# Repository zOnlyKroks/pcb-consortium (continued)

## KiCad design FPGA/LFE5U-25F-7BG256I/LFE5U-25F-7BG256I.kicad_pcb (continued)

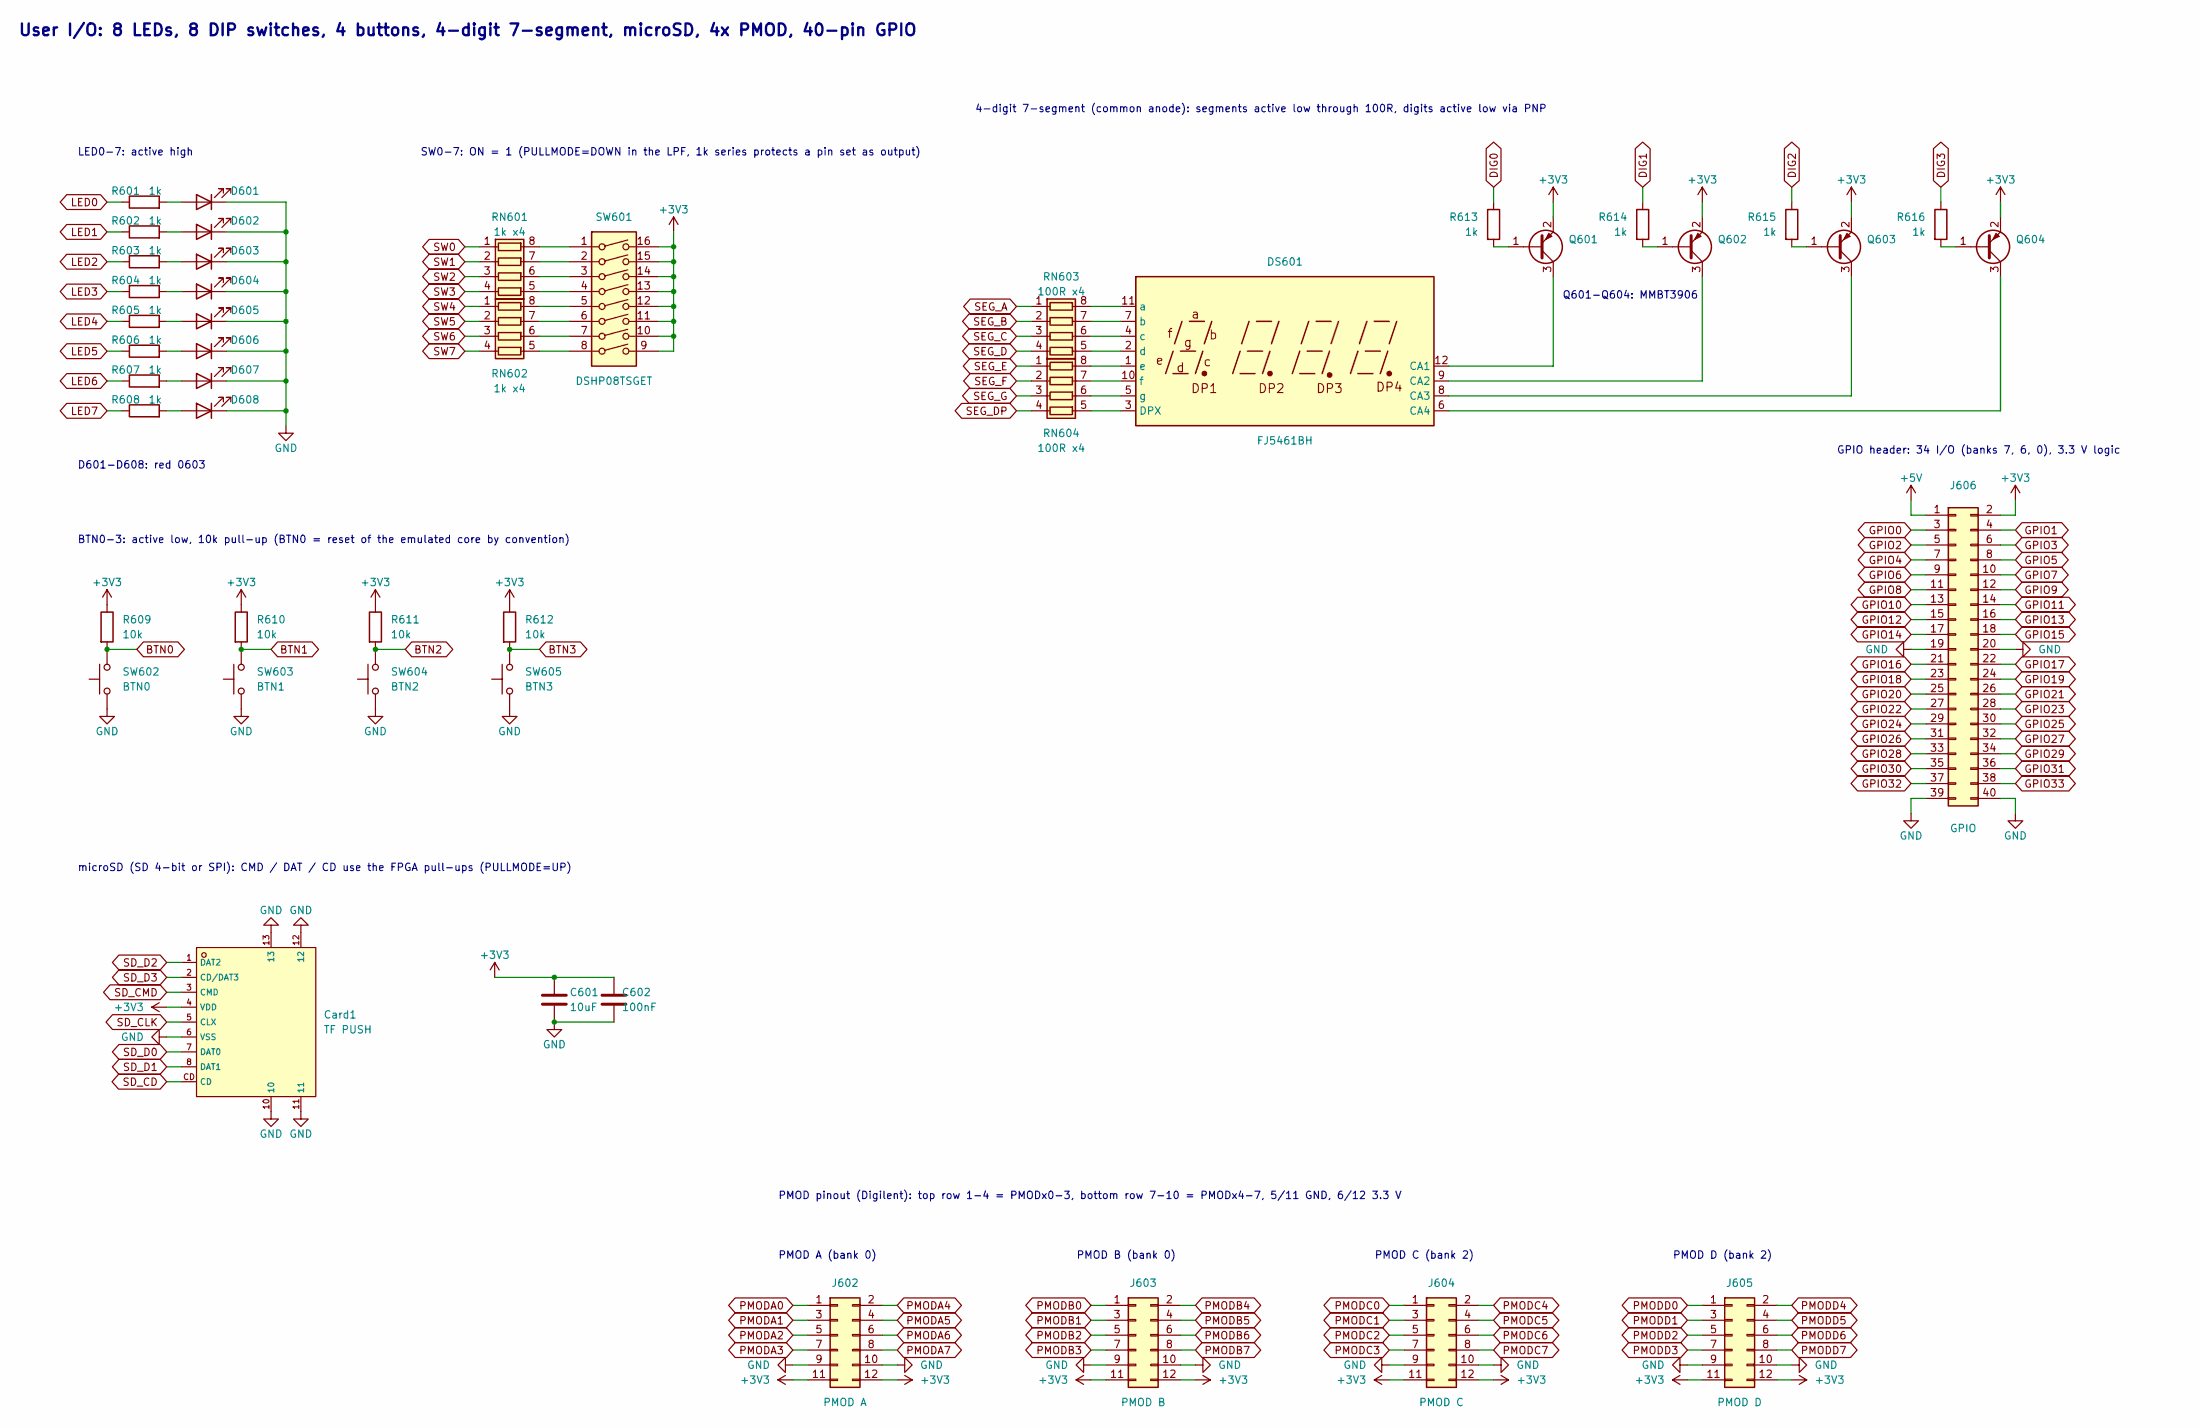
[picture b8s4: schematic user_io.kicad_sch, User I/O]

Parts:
C601: 10uF; C_0603_1608Metric; LCSC Part # C19702
C602: 100nF; C_0603_1608Metric; LCSC Part # C14663
Card1: TF PUSH; C393941_TF-SMD_TF-PUSH; LCSC C393941
D601, D602, D603, D604, D605, D606, D607, D608: LED red; LED_0603_1608Metric; LCSC Part # C2286
DS601: FJ5461BH; CA56-12EWA; LCSC Part # C38183
J602: PMOD A; PinSocket_2x06_P2.54mm_Horizontal; LCSC Part # C2897426
J603: PMOD B; PinSocket_2x06_P2.54mm_Horizontal; LCSC Part # C2897426
J604: PMOD C; PinSocket_2x06_P2.54mm_Horizontal; LCSC Part # C2897426
J605: PMOD D; PinSocket_2x06_P2.54mm_Horizontal; LCSC Part # C2897426
J606: GPIO; PinHeader_2x20_P2.54mm_Vertical; LCSC Part # C22465944
Q601, Q602, Q603, Q604: MMBT3906; SOT-23; LCSC Part # C53444
R601, R602, R603, R604, R605, R606, R607, R608, R613, R614, R615, R616: 1k; R_0603_1608Metric; LCSC Part # C22548
R609, R610, R611, R612: 10k; R_0603_1608Metric; LCSC Part # C25804
RN601, RN602: 1k x4; R_Array_Convex_4x0603; LCSC Part # C20197
RN603, RN604: 100R x4; R_Array_Convex_4x0603; LCSC Part # C25506
SW601: DSHP08TSGET; SW_DIP_SPSTx08_Slide_KingTek_DSHP08TS_W7.62mm_P1.27mm; LCSC Part # C40738
SW602: BTN0; SW_SPST_TL3342; LCSC Part # C318884
SW603: BTN1; SW_SPST_TL3342; LCSC Part # C318884
SW604: BTN2; SW_SPST_TL3342; LCSC Part # C318884
SW605: BTN3; SW_SPST_TL3342; LCSC Part # C318884

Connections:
+3V3: C601.1, C602.1, Card1.4 (VDD), J602.11, J602.12, J603.11, J603.12, J604.11, J604.12, J605.11, J605.12, J606.2, Q601.2 (E), Q602.2 (E), Q603.2 (E), Q604.2 (E), R609.1, R610.1, R611.1, R612.1, SW601.9, SW601.10, SW601.11, SW601.12, SW601.13, SW601.14, SW601.15, SW601.16; also elsewhere on the board
+5V: J606.1; also elsewhere on the board
BTN0: R609.2, SW602.2; also elsewhere on the board
BTN1: R610.2, SW603.2; also elsewhere on the board
BTN2: R611.2, SW604.2; also elsewhere on the board
BTN3: R612.2, SW605.2; also elsewhere on the board
DIG0: R613.1; also elsewhere on the board
DIG1: R614.1; also elsewhere on the board
DIG2: R615.1; also elsewhere on the board
DIG3: R616.1; also elsewhere on the board
GND: C601.2, C602.2, Card1.6 (VSS), Card1.10, Card1.11, Card1.12, Card1.13, D601.1 (K), D602.1 (K), D603.1 (K), D604.1 (K), D605.1 (K), D606.1 (K), D607.1 (K), D608.1 (K), J602.9, J602.10, J603.9, J603.10, J604.9, J604.10, J605.9, J605.10, J606.19, J606.20, J606.39, J606.40, SW602.1, SW603.1, SW604.1, SW605.1; also elsewhere on the board
GPIO0: J606.3; also elsewhere on the board
GPIO1: J606.4; also elsewhere on the board
GPIO2: J606.5; also elsewhere on the board
GPIO3: J606.6; also elsewhere on the board
GPIO4: J606.7; also elsewhere on the board
GPIO5: J606.8; also elsewhere on the board
GPIO6: J606.9; also elsewhere on the board
GPIO7: J606.10; also elsewhere on the board
GPIO8: J606.11; also elsewhere on the board
GPIO9: J606.12; also elsewhere on the board
GPIO10: J606.13; also elsewhere on the board
GPIO11: J606.14; also elsewhere on the board
GPIO12: J606.15; also elsewhere on the board
GPIO13: J606.16; also elsewhere on the board
GPIO14: J606.17; also elsewhere on the board
GPIO15: J606.18; also elsewhere on the board
GPIO16: J606.21; also elsewhere on the board
GPIO17: J606.22; also elsewhere on the board
GPIO18: J606.23; also elsewhere on the board
GPIO19: J606.24; also elsewhere on the board
GPIO20: J606.25; also elsewhere on the board
GPIO21: J606.26; also elsewhere on the board
GPIO22: J606.27; also elsewhere on the board
GPIO23: J606.28; also elsewhere on the board
GPIO24: J606.29; also elsewhere on the board
GPIO25: J606.30; also elsewhere on the board
GPIO26: J606.31; also elsewhere on the board
GPIO27: J606.32; also elsewhere on the board
GPIO28: J606.33; also elsewhere on the board
GPIO29: J606.34; also elsewhere on the board
GPIO30: J606.35; also elsewhere on the board
GPIO31: J606.36; also elsewhere on the board
GPIO32: J606.37; also elsewhere on the board
GPIO33: J606.38; also elsewhere on the board
LED0: R601.1; also elsewhere on the board
LED1: R602.1; also elsewhere on the board
LED2: R603.1; also elsewhere on the board
LED3: R604.1; also elsewhere on the board
LED4: R605.1; also elsewhere on the board
LED5: R606.1; also elsewhere on the board
LED6: R607.1; also elsewhere on the board
LED7: R608.1; also elsewhere on the board
unnamed: D601.2 (A), R601.2
unnamed: D602.2 (A), R602.2
unnamed: D603.2 (A), R603.2
unnamed: D604.2 (A), R604.2
unnamed: D605.2 (A), R605.2
unnamed: D606.2 (A), R606.2
unnamed: D607.2 (A), R607.2
unnamed: D608.2 (A), R608.2
unnamed: DS601.12 (CA1), Q601.3 (C)
unnamed: DS601.9 (CA2), Q602.3 (C)
unnamed: DS601.8 (CA3), Q603.3 (C)
unnamed: DS601.6 (CA4), Q604.3 (C)
unnamed: DS601.3 (DPX), RN604.5 (R4.2)
unnamed: DS601.11 (a), RN603.8 (R1.2)
unnamed: DS601.7 (b), RN603.7 (R2.2)
unnamed: DS601.4 (c), RN603.6 (R3.2)
unnamed: DS601.2 (d), RN603.5 (R4.2)
unnamed: DS601.1 (e), RN604.8 (R1.2)
unnamed: DS601.10 (f), RN604.7 (R2.2)
unnamed: DS601.5 (g), RN604.6 (R3.2)
unnamed: Q601.1 (B), R613.2
unnamed: Q602.1 (B), R614.2
unnamed: Q603.1 (B), R615.2
unnamed: Q604.1 (B), R616.2
unnamed: RN601.8 (R1.2), SW601.1
unnamed: RN601.7 (R2.2), SW601.2
unnamed: RN601.6 (R3.2), SW601.3
unnamed: RN601.5 (R4.2), SW601.4
unnamed: RN602.8 (R1.2), SW601.5
unnamed: RN602.7 (R2.2), SW601.6
unnamed: RN602.6 (R3.2), SW601.7
unnamed: RN602.5 (R4.2), SW601.8
PMODA0: J602.1; also elsewhere on the board
PMODA1: J602.3; also elsewhere on the board
PMODA2: J602.5; also elsewhere on the board
PMODA3: J602.7; also elsewhere on the board
PMODA4: J602.2; also elsewhere on the board
PMODA5: J602.4; also elsewhere on the board
PMODA6: J602.6; also elsewhere on the board
PMODA7: J602.8; also elsewhere on the board
PMODB0: J603.1; also elsewhere on the board
PMODB1: J603.3; also elsewhere on the board
PMODB2: J603.5; also elsewhere on the board
PMODB3: J603.7; also elsewhere on the board
PMODB4: J603.2; also elsewhere on the board
PMODB5: J603.4; also elsewhere on the board
PMODB6: J603.6; also elsewhere on the board
PMODB7: J603.8; also elsewhere on the board
PMODC0: J604.1; also elsewhere on the board
PMODC1: J604.3; also elsewhere on the board
PMODC2: J604.5; also elsewhere on the board
PMODC3: J604.7; also elsewhere on the board
PMODC4: J604.2; also elsewhere on the board
PMODC5: J604.4; also elsewhere on the board
PMODC6: J604.6; also elsewhere on the board
PMODC7: J604.8; also elsewhere on the board
PMODD0: J605.1; also elsewhere on the board
PMODD1: J605.3; also elsewhere on the board
PMODD2: J605.5; also elsewhere on the board
PMODD3: J605.7; also elsewhere on the board
PMODD4: J605.2; also elsewhere on the board
PMODD5: J605.4; also elsewhere on the board
PMODD6: J605.6; also elsewhere on the board
PMODD7: J605.8; also elsewhere on the board
SD_CD: Card1.CD; also elsewhere on the board
SD_CLK: Card1.5 (CLX); also elsewhere on the board
SD_CMD: Card1.3 (CMD); also elsewhere on the board
SD_D0: Card1.7 (DAT0); also elsewhere on the board
SD_D1: Card1.8 (DAT1); also elsewhere on the board
SD_D2: Card1.1 (DAT2); also elsewhere on the board
SD_D3: Card1.2 (CD/DAT3); also elsewhere on the board
SEG_A: RN603.1 (R1.1); also elsewhere on the board
SEG_B: RN603.2 (R2.1); also elsewhere on the board
SEG_C: RN603.3 (R3.1); also elsewhere on the board
SEG_D: RN603.4 (R4.1); also elsewhere on the board
SEG_DP: RN604.4 (R4.1); also elsewhere on the board
SEG_E: RN604.1 (R1.1); also elsewhere on the board
SEG_F: RN604.2 (R2.1); also elsewhere on the board
SEG_G: RN604.3 (R3.1); also elsewhere on the board
SW0: RN601.1 (R1.1); also elsewhere on the board
SW1: RN601.2 (R2.1); also elsewhere on the board
SW2: RN601.3 (R3.1); also elsewhere on the board
SW3: RN601.4 (R4.1); also elsewhere on the board
SW4: RN602.1 (R1.1); also elsewhere on the board
SW5: RN602.2 (R2.1); also elsewhere on the board
SW6: RN602.3 (R3.1); also elsewhere on the board
SW7: RN602.4 (R4.1); also elsewhere on the board

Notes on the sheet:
PMOD B (bank 0)
PMOD pinout (Digilent): top row 1-4 = PMODx0-3, bottom row 7-10 = PMODx4-7, 5/11 GND, 6/12 3.3 V
PMOD C (bank 2)
Q601-Q604: MMBT3906
PMOD A (bank 0)
D601-D608: red 0603
microSD (SD 4-bit or SPI): CMD / DAT / CD use the FPGA pull-ups (PULLMODE=UP)
BTN0-3: active low, 10k pull-up (BTN0 = reset of the emulated core by convention)
User I/O: 8 LEDs, 8 DIP switches, 4 buttons, 4-digit 7-segment, microSD, 4x PMOD, 40-pin GPIO
GPIO header: 34 I/O (banks 7, 6, 0), 3.3 V logic
PMOD D (bank 2)
LED0-7: active high
SW0-7: ON = 1 (PULLMODE=DOWN in the LPF, 1k series protects a pin set as output)
4-digit 7-segment (common anode): segments active low through 100R, digits active low via PNP

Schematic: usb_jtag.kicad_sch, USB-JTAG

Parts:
C301: 10uF; C_0603_1608Metric; LCSC Part # C19702
C302, C303: 22pF; C_0603_1608Metric; LCSC Part # C1653
C304, C305: 100nF; C_0603_1608Metric; LCSC Part # C14663
F301: 1.1A; Fuse_1206_3216Metric; LCSC Part # C20801
J301: TYPE-C-31-M-12; USB_C_Receptacle_HRO_TYPE-C-31-M-12; LCSC Part # C165948
J302: JTAG; PinHeader_1x06_P2.54mm_Vertical; LCSC Part # C492405
R302, R303: 5.1k; R_0603_1608Metric; LCSC Part # C23186
U301: CH347F; QFN-28-1EP_4x4mm_P0.4mm_EP2.4x2.4mm; LCSC Part # C18221627
U302: USBLC6-2SC6; SOT-23-6; LCSC Part # C2687116
Y301: 8MHz; Crystal_SMD_3225-4Pin_3.2x2.5mm; MPN X32258MSB4SI; LCSC Part # C2682774

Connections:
+3V3: C304.1, C305.1, J302.1, U301.6 (VIO), U301.21 (VCC); also elsewhere on the board
+5V: C301.1, F301.2, U302.5 (VBUS); also elsewhere on the board
CH_CTS: U301.17 (~CTS0/GPIO0); also elsewhere on the board
CH_MISO: U301.15 (MISO); also elsewhere on the board
CH_MOSI: U301.16 (MOSI); also elsewhere on the board
CH_RTS: U301.18 (~RTS0/GPIO1); also elsewhere on the board
CH_RXD: U301.22 (RXD0); also elsewhere on the board
CH_SCK: U301.14 (SCK); also elsewhere on the board
CH_SCS: U301.13 (SCS0); also elsewhere on the board
CH_TXD: U301.19 (TXD0); also elsewhere on the board
GND: C301.2, C302.2, C303.2, C304.2, C305.2, J301.A1 (GND), J301.A12 (GND), J301.B1 (GND), J301.B12 (GND), J301.SH (SHIELD), J302.6, R302.2, R303.2, U301.20 (GND), U301.29 (EP), U302.2 (GND), Y301.2 (G), Y301.4 (G); also elsewhere on the board
JTAG_TCK: J302.2, U301.23 (TCK); also elsewhere on the board
JTAG_TDI: J302.3, U301.25 (TDI); also elsewhere on the board
JTAG_TDO: J302.4, U301.24 (TDO); also elsewhere on the board
JTAG_TMS: J302.5, U301.26 (TMS); also elsewhere on the board
unnamed: F301.1, J301.A4 (VBUS), J301.A9 (VBUS), J301.B4 (VBUS), J301.B9 (VBUS)
unnamed: J301.A5 (CC1), R302.1
unnamed: J301.B5 (CC2), R303.1
unnamed: J301.A6 (D+), J301.B6 (D+), U302.3 (I/O2)
unnamed: J301.A7 (D-), J301.B7 (D-), U302.1 (I/O1)
unnamed: U301.28 (UD+), U302.4 (I/O2)
unnamed: U301.27 (UD-), U302.6 (I/O1)
unnamed: C302.1, U301.1 (XI), Y301.1
unnamed: C303.1, U301.2 (XO), Y301.3

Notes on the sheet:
CH_TXD = CH347 TXD0 (FPGA receives), CH_RXD = CH347 RXD0
J302: external JTAG (Lattice / FTDI cable)
UD+/UD-: no series resistors
+5 V, 1.1 A PTC
USB-C: board power + CH347F (USB 2.0 high speed). JTAG -> ECP5 (openFPGALoader -c ch347, OpenOCD ch347),
Soft-core debug (e.g. VexRiscv / RISC-V debug) goes through the ECP5 JTAGG primitive on this same chain.
1 VREF 2 TCK 3 TDI 4 TDO 5 TMS 6 GND
VCC + VIO = 3.3 V: 100 nF each at the pins
UART0 + SPI -> bank 7 for the emulated core (console / debug bridge). All interfaces work at the same time.

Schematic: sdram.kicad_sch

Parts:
C401: 10uF; C_0603_1608Metric; LCSC Part # C19702
C402, C403, C404, C405, C406, C407, C408: 100nF; C_0603_1608Metric; LCSC Part # C14663
U401: W9812G6KH-6; TSOP-II-54_22.2x10.16mm_P0.8mm; LCSC Part # C62379

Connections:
+3V3: C401.1, C402.1, C403.1, C404.1, C405.1, C406.1, C407.1, C408.1, U401.1 (VDD), U401.3 (VDDQ), U401.9 (VDDQ), U401.14 (VDD), U401.27 (VDD), U401.43 (VDDQ), U401.49 (VDDQ); also elsewhere on the board
GND: C401.2, C402.2, C403.2, C404.2, C405.2, C406.2, C407.2, C408.2, U401.6 (VSSQ), U401.12 (VSSQ), U401.28 (VSS), U401.41 (VSS), U401.46 (VSSQ), U401.52 (VSSQ), U401.54 (VSS); also elsewhere on the board
RAM_A0: U401.23 (A0); also elsewhere on the board
RAM_A1: U401.24 (A1); also elsewhere on the board
RAM_A2: U401.25 (A2); also elsewhere on the board
RAM_A3: U401.26 (A3); also elsewhere on the board
RAM_A4: U401.29 (A4); also elsewhere on the board
RAM_A5: U401.30 (A5); also elsewhere on the board
RAM_A6: U401.31 (A6); also elsewhere on the board
RAM_A7: U401.32 (A7); also elsewhere on the board
RAM_A8: U401.33 (A8); also elsewhere on the board
RAM_A9: U401.34 (A9); also elsewhere on the board
RAM_A10: U401.22 (A10/AP); also elsewhere on the board
RAM_A11: U401.35 (A11); also elsewhere on the board
RAM_BA0: U401.20 (BS0); also elsewhere on the board
RAM_BA1: U401.21 (BS1); also elsewhere on the board
RAM_CASn: U401.17 (~CAS); also elsewhere on the board
RAM_CKE: U401.37 (CKE); also elsewhere on the board
RAM_CLK: U401.38 (CLK); also elsewhere on the board
RAM_CSn: U401.19 (~CS); also elsewhere on the board
RAM_DQ0: U401.2 (DQ0); also elsewhere on the board
RAM_DQ1: U401.4 (DQ1); also elsewhere on the board
RAM_DQ2: U401.5 (DQ2); also elsewhere on the board
RAM_DQ3: U401.7 (DQ3); also elsewhere on the board
RAM_DQ4: U401.8 (DQ4); also elsewhere on the board
RAM_DQ5: U401.10 (DQ5); also elsewhere on the board
RAM_DQ6: U401.11 (DQ6); also elsewhere on the board
RAM_DQ7: U401.13 (DQ7); also elsewhere on the board
RAM_DQ8: U401.42 (DQ8); also elsewhere on the board
RAM_DQ9: U401.44 (DQ9); also elsewhere on the board
RAM_DQ10: U401.45 (DQ10); also elsewhere on the board
RAM_DQ11: U401.47 (DQ11); also elsewhere on the board
RAM_DQ12: U401.48 (DQ12); also elsewhere on the board
RAM_DQ13: U401.50 (DQ13); also elsewhere on the board
RAM_DQ14: U401.51 (DQ14); also elsewhere on the board
RAM_DQ15: U401.53 (DQ15); also elsewhere on the board
RAM_DQMH: U401.39 (UDQM); also elsewhere on the board
RAM_DQML: U401.15 (LDQM); also elsewhere on the board
RAM_RASn: U401.18 (~RAS); also elsewhere on the board
RAM_WEn: U401.16 (~WE); also elsewhere on the board

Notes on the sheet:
TSOP-II-54, A0-A11. The 32 MB W9825G6KH-6 fits the same footprint; it needs A12 on pin 36 (spare ball M15).
16 MB SDR SDRAM, 16 bit (W9812G6KH-6, 166 MHz) on banks 3 / 2
Decoupling: one 100 nF per VDD / VDDQ pin (7) + bulk
Keep RAM_CLK short; a series resistor can be added at layout.

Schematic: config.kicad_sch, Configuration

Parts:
C101, C102: 100nF; C_0603_1608Metric; LCSC Part # C14663
D101: LED red; LED_0603_1608Metric; LCSC Part # C2286
Q101: 2N7002; SOT-23; LCSC Part # C8545
R101, R102, R103, R104, R105, R106, R107, R111, R112: 10k; R_0603_1608Metric; LCSC Part # C25804
R108: 1k; R_0603_1608Metric; LCSC Part # C22548
R109: 100R; R_0603_1608Metric; LCSC Part # C22775
R110: 2.2k; R_0603_1608Metric; LCSC Part # C4190
SW101: PROG; SW_SPST_TL3342; LCSC Part # C318884
U101: W25Q32JVSSIQ; SOIC-8_5.3x5.3mm_P1.27mm; LCSC Part # C179173
X101: 25MHz; Oscillator_SMD_Abracon_ASE-4Pin_3.2x2.5mm; MPN OT322525MJBA4SL; LCSC Part # C669088

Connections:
+3V3: C101.1, C102.1, R101.1, R103.1, R105.1, R106.1, R107.1, R108.1, R111.1, R112.1, U101.8 (VCC), X101.1 (EN), X101.4 (Vdd); also elsewhere on the board
CFG0: R102.1; also elsewhere on the board
CFG1: R103.2; also elsewhere on the board
CFG2: R104.1; also elsewhere on the board
CLK25: R109.2; also elsewhere on the board
DONE: Q101.1 (G), R107.2; also elsewhere on the board
FLASH_CLK: U101.6 (CLK); also elsewhere on the board
FLASH_CSn: R101.2, U101.1 (~CS); also elsewhere on the board
FLASH_IO0: U101.5 (DI/IO_{0}); also elsewhere on the board
FLASH_IO1: U101.2 (DO/IO_{1}); also elsewhere on the board
FLASH_IO2: U101.3 (~WP/IO_{2}); also elsewhere on the board
FLASH_IO3: U101.7 (~HOLD/~RESET/IO_{3}); also elsewhere on the board
GND: C101.2, C102.2, Q101.2 (S), R102.2, R104.2, R110.2, SW101.1, U101.4 (GND), X101.2 (GND); also elsewhere on the board
INITN: R106.2; also elsewhere on the board
JTAG_TCK: R110.1; also elsewhere on the board
JTAG_TDI: R112.2; also elsewhere on the board
JTAG_TMS: R111.2; also elsewhere on the board
unnamed: D101.2 (A), R108.2
unnamed: D101.1 (K), Q101.3 (D)
unnamed: R109.1, X101.3 (OUT)
PROGRAMN: R105.2, SW101.2; also elsewhere on the board

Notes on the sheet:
DONE: LED on when configured
25 MHz system clock -> ball P6 (PLL input LLC_GPLL0T_IN)
INITN
PROGRAMN: button reloads the bitstream
Bitstream (~0.6 MB) + user flash (W25Q32JV-IQ: QE=1 from the factory, so IO2/IO3 need no pull-ups)
JTAG: TCK pulled low, TMS / TDI pulled high
Configuration: master SPI from 4 MB QSPI flash, PROGRAMN / INITN / DONE, 25 MHz clock
CFG[2:0] = 010 -> master SPI boot

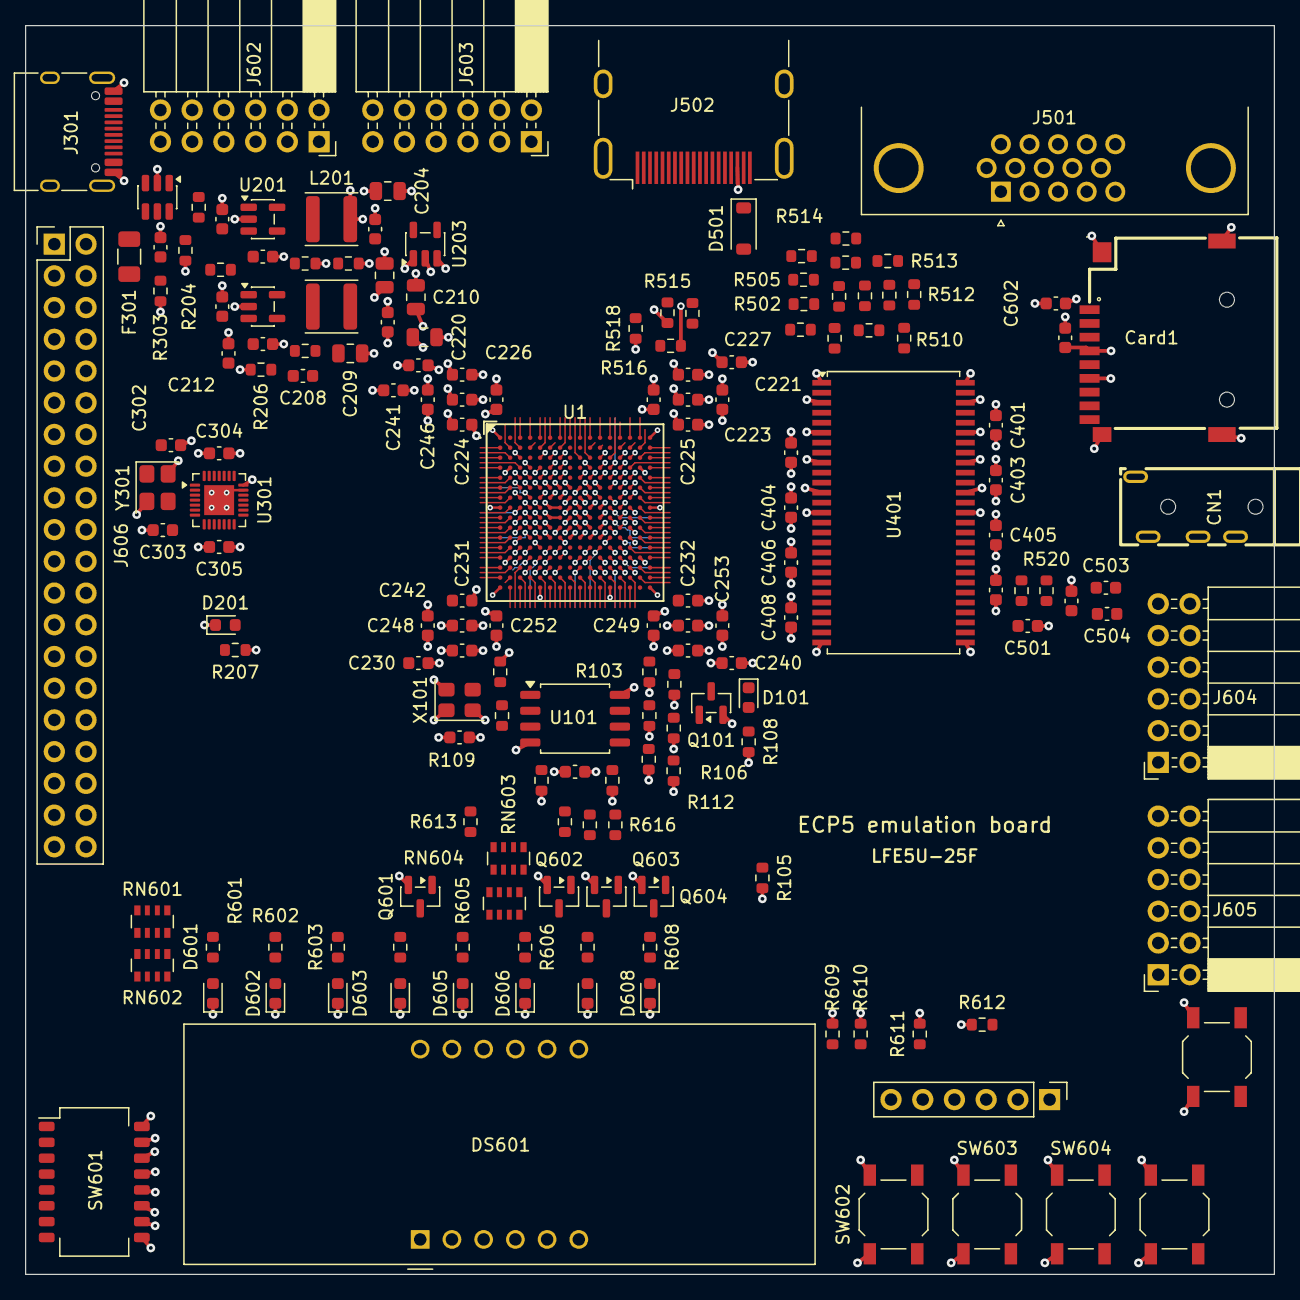
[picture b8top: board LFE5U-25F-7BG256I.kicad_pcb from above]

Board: 6 copper layers, 100.0 x 100.0 mm, 167 parts (0 on the bottom side), 262 nets.

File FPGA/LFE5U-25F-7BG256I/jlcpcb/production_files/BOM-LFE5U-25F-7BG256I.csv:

Comment,Designator,Footprint,LCSC,Quantity
1.1A,F301,Fuse_1206_3216Metric,C20801,1
100R,"R109,R513,R514",R_0603_1608Metric,C22775,3
100R x4,"RN603,RN604",R_Array_Convex_4x0603,C25506,2
100k,"R201,R204",R_0603_1608Metric,C25803,2
100k 1%,R202,R_0603_1608Metric,C25803,1
100nF,"C101,C102,C202,C207,C222,C223,C224,C225,C226,C227,C231,C232,C242,C243,C244,C245,C246,C247,C248,C249,C250,C251,C252,C253,C254,C304,C305,C402,C403,C404,C405,C406,C407,C408,C602",C_0603_1608Metric,C14663,35
10k,"R101,R102,R103,R104,R105,R106,R107,R111,R112,R609,R610,R611,R612",R_0603_1608Metric,C25804,13
10k 1%,R205,R_0603_1608Metric,C25804,1
10nF,"C501,C502",C_0603_1608Metric,C1589,2
10uF,"C201,C206,C211,C212,C221,C230,C240,C241,C301,C401,C503,C504,C601",C_0603_1608Metric,C19702,13
12k,R517,R_0603_1608Metric,C22790,1
12k 1%,R206,R_0603_1608Metric,C22790,1
1k,"R108,R207,R502,R506,R510,R601,R602,R603,R604,R605,R606,R607,R608,R613,R614,R615,R616",R_0603_1608Metric,C22548,17
1k x4,"RN601,RN602",R_Array_Convex_4x0603,C20197,2
2.2k,"R110,R515,R516",R_0603_1608Metric,C4190,3
2.2uH,"L201,L202",L_Changjiang_FNR4020S,C167825,2
22k,R518,R_0603_1608Metric,C31850,1
22k 1%,R203,R_0603_1608Metric,C31850,1
22pF,"C203,C208,C302,C303",C_0603_1608Metric,C1653,4
22uF,"C204,C205,C209,C210,C220",C_0805_2012Metric,C380338,5
25MHz,X101,Oscillator_SMD_Abracon_ASE-4Pin_3.2x2.5mm,C669088,1
2N7002,Q101,SOT-23,C8545,1
2k,"R503,R507,R511",R_0603_1608Metric,C22975,3
3.9k,"R504,R508,R512",R_0603_1608Metric,C23018,3
470R,"R519,R520",R_0603_1608Metric,C23179,2
5.1k,"R302,R303",R_0603_1608Metric,C23186,2
510R,"R501,R505,R509",R_0603_1608Metric,C23193,3
8MHz,Y301,Crystal_SMD_3225-4Pin_3.2x2.5mm,C2682774,1
AP2112K-2.5TRG1,U203,SOT-23-5,C176945,1
B5819W,D501,D_SOD-123,C64885,1
BTN0,SW602,SW_SPST_TL3342,C318884,1
BTN1,SW603,SW_SPST_TL3342,C318884,1
BTN2,SW604,SW_SPST_TL3342,C318884,1
BTN3,SW605,SW_SPST_TL3342,C318884,1
CH347F,U301,QFN-28-1EP_4x4mm_P0.4mm_EP2.4x2.4mm,C18221627,1
DSHP08TSGET,SW601,SW_DIP_SPSTx08_Slide_KingTek_DSHP08TS_W7.62mm_P1.27mm,C40738,1
FJ5461BH,DS601,CA56-12EWA,C38183,1
GPIO,J606,PinHeader_2x20_P2.54mm_Vertical,C22465944,1
HDMI-A,J502,HDMI_A_Molex_208658-1001_Horizontal,C138388,1
JTAG,J302,PinHeader_1x06_P2.54mm_Vertical,C492405,1
LED red,"D101,D201,D601,D602,D603,D604,D605,D606,D607,D608",LED_0603_1608Metric,C2286,10
LFE5U-25F-6BG256C,U1,C1550762_CABGA-256_L14_0-W14_0-R16-C16-P0_80-TL,C1550762,1
MMBT3906,"Q601,Q602,Q603,Q604",SOT-23,C53444,4
PJ-320A,CN1,C2884926_AUDIO-TH_XKB_PJ-320A,C2884926,1
PMOD A,J602,PinSocket_2x06_P2.54mm_Horizontal,C2897426,1
PMOD B,J603,PinSocket_2x06_P2.54mm_Horizontal,C2897426,1
PMOD C,J604,PinSocket_2x06_P2.54mm_Horizontal,C2897426,1
PMOD D,J605,PinSocket_2x06_P2.54mm_Horizontal,C2897426,1
PROG,SW101,SW_SPST_TL3342,C318884,1
SY8089A1AAC,"U201,U202",SOT-23-5,C479074,2
TF PUSH,Card1,C393941_TF-SMD_TF-PUSH,C393941,1
TYPE-C-31-M-12,J301,USB_C_Receptacle_HRO_TYPE-C-31-M-12,C165948,1
USBLC6-2SC6,U302,SOT-23-6,C2687116,1
VGA,J501,DSUB-15-HD_Socket_Horizontal_P2.29x1.90mm_EdgePinOffset3.03mm_Housed_MountingHolesOffset4.94mm,C379814,1
W25Q32JVSSIQ,U101,SOIC-8_5.3x5.3mm_P1.27mm,C179173,1
W9812G6KH-6,U401,TSOP-II-54_22.2x10.16mm_P0.8mm,C62379,1

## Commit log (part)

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2026-02-17 Init
2026-02-18 Shenanigans ensued
2026-02-18 Get reverse polarity detected
2026-02-18 Ues jlcpcb basic part where applicable
2026-02-19 Standalone circuit
2026-02-20 Better library
2026-02-20 Central lib
2026-03-04 yeet
2026-03-04 You slongoid
2026-03-05 Shiver his timbers!
2026-03-05 May god have mercy on my soul
2026-03-05 wee woo
2026-03-05 afawj
2026-03-05 shivers got timbered
2026-03-06 The so called shenanigooner
2026-03-07 basti
2026-03-08 Radio
2026-03-09 RAAAA
2026-03-10 BRRRR
2026-03-10 started pcb routing
2026-03-10 FM radio
2026-03-10 Smaller components
2026-03-10 go go gadget routing
2026-03-11 AAAAAAAAAAAAAA
2026-03-11 Yarrr harrr
2026-03-12 progress on pcb
2026-03-14 Shing shong
2026-03-14 Filter
2026-03-15 Aux In gefixt
2026-03-15 Shenanigooner
2026-03-16 Ra ra rasputin
2026-03-17 Rasputin
2026-03-17 Active rectifier that shall never be built
2026-03-17 rararararara
2026-03-19 Create README.md with project information
    Added README file with project details and usage guidelines.
2026-03-19 Add LICENSE file
2026-03-19 Simplify README by removing license and disclaimer
    Removed licensing details and disclaimer from README.
2026-03-20 wajfawj
2026-03-23 Idiotencheck 1
2026-03-23 fajhw
2026-03-23 fajwenj
2026-03-26 fjaoiwe
2026-03-27 yarrr
2026-03-27 yarrrr
2026-03-30 Production v2 radio
2026-03-30 First production
2026-04-20 afjj
2026-04-22 Yarr
2026-04-22 rereredesigner
2026-04-22 All hail lcsc
2026-04-28 Shenanigans
2026-04-30 FM Radio v2
2026-04-30 ESP32 Wechsel angefangen
2026-05-06 Routing of board revision 2 complete
2026-05-08 Idiotencheck #1
2026-05-08 Second order
2026-05-11 hofoa
2026-05-12 TENNE HEKO BANZAIII
2026-05-12 LT Spicing
2026-05-13 jfja
2026-05-14 add cern-kicad-libs submodule and update workspace state
2026-05-17 RAAAA2
2026-05-18 plep
2026-05-18 grrr
2026-05-21 Ach basti
2026-05-22 Grrr basti, grrr
2026-05-26 FPGA
2026-05-27 fhewh2
2026-05-31 FPGA time
2026-06-01 fhja
2026-06-02 DA14AVDDECT
2026-06-03 jfaj
2026-06-04 fdajfrjw
2026-06-04 Production Values
2026-06-05 Rework some trace lines for wider with in high amperage environments
2026-06-05 reroute
2026-06-05 finish
2026-06-07 Try fixes
2026-06-09 4 layer
2026-06-09 basti hat drueber geguckt
2026-06-13 Rev 2 of ch224k)
2026-06-14 fdcj
2026-06-14 cfja
2026-06-15 re-gerber
2026-06-17 dfja
2026-06-21 dfjaj
2026-06-21 afdj
2026-06-25 jajw
2026-06-25 Hail mary
2026-06-25 hail mary 2
2026-06-26 Use library
2026-06-26 2fjj
2026-06-26 readd new old code
2026-06-28 jdfajjj
